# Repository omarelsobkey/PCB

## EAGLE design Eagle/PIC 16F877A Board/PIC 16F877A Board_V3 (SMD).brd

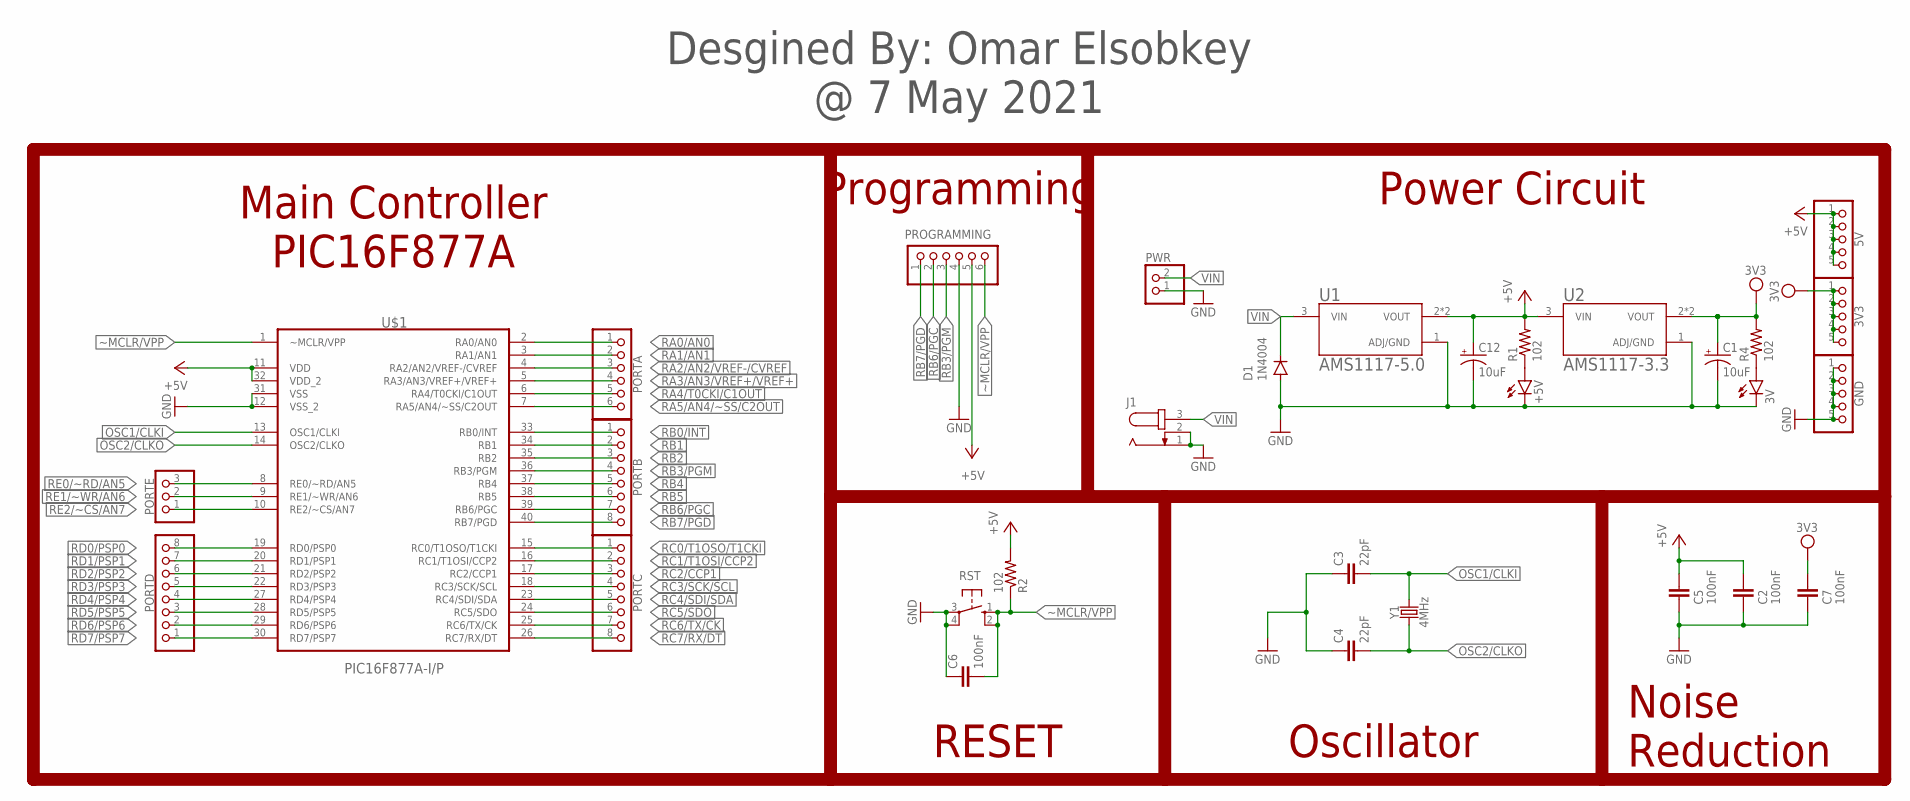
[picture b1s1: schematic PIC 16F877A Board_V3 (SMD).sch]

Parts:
3V: LEDSML0805; SML0805
3V3, 5V: PINHD-1X5; 1X05
+5V: LEDSML0805; SML0805
C1, C12: 10uF; CPOL-RADIAL-2.5MM-5MM-KIT
C2, C5, C6, C7: 100nF; C025-025X050
C3, C4: 22pF; C025-025X050
D1: 1N4004; DO41-10
GND: PINHD-1X5; 1X05
J1: JACK-PLUG0; SPC4077
PORTA: PINHD-1X6; 1X06
PORTB: PINHD-1X8; 1X08
PORTC: PINHD-1X8; 1X08
PORTD: PINHD-1X8; 1X08
PORTE: PINHD-1X3; 1X03
PROGRAMMING: PINHD-1X6; 1X06
PWR: PINHD-1X2; 1X02
R1, R2, R4: 102; 1206
RST: 10-XX; B3F-10XX
U1: AMS1117-5.0
U2: AMS1117-3.3; AMS1117-5.0
U$1: PIC16F877A-I/P; 16F877A
Y1: 4MHz; HC49U

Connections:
3V3: 3V3.1, 3V3.2, 3V3.3, 3V3.4, 3V3.5, C1.1 (+), C7.2, R4.2, U2.2 (VOUT), U2.4 (VOUT)
+5V: 5V.1, 5V.2, 5V.3, 5V.4, 5V.5, C2.2, C5.2, C12.1 (+), PROGRAMMING.5, R1.2, R2.2, U1.2 (VOUT), U1.4 (VOUT), U2.3 (VIN), U$1.11 (VDD), U$1.32 (VDD_2)
GND: 3V.C, +5V.C, C1.2 (-), C2.1, C3.1, C4.1, C5.1, C6.1, C7.1, C12.2 (-), D1.A, GND.1, GND.2, GND.3, GND.4, GND.5, J1.1, J1.2, PROGRAMMING.4, PWR.1, RST.3, RST.4 (P1), U1.1 (ADJ/GND), U2.1 (ADJ/GND), U$1.12 (VSS_2), U$1.31 (VSS)
unnamed: 3V.A, R4.1
unnamed: +5V.A, R1.1
OSC1/CLKI: C3.2, U$1.13 (OSC1/CLKI), Y1.2
OSC2/CLKO: C4.2, U$1.14 (OSC2/CLKO), Y1.1
RA0/AN0: PORTA.1, U$1.2 (RA0/AN0)
RA1/AN1: PORTA.2, U$1.3 (RA1/AN1)
RA2/AN2/VREF-/CVREF: PORTA.3, U$1.4 (RA2/AN2/VREF-/CVREF)
RA3/AN3/VREF+/VREF+: PORTA.4, U$1.5 (RA3/AN3/VREF+/VREF+)
RA4/T0CKI/C1OUT: PORTA.5, U$1.6 (RA4/T0CKI/C1OUT)
RA5/AN4/~SS/C2OUT: PORTA.6, U$1.7 (RA5/AN4/~SS/C2OUT)
RB0/INT: PORTB.1, U$1.33 (RB0/INT)
RB1: PORTB.2, U$1.34 (RB1)
RB2: PORTB.3, U$1.35 (RB2)
RB3/PGM: PORTB.4, PROGRAMMING.3, U$1.36 (RB3/PGM)
RB4: PORTB.5, U$1.37 (RB4)
RB5: PORTB.6, U$1.38 (RB5)
RB6/PGC: PORTB.7, PROGRAMMING.2, U$1.39 (RB6/PGC)
RB7/PGD: PORTB.8, PROGRAMMING.1, U$1.40 (RB7/PGD)
RC0/T1OSO/T1CKI: PORTC.1, U$1.15 (RC0/T1OSO/T1CKI)
RC1/T1OSI/CCP2: PORTC.2, U$1.16 (RC1/T1OSI/CCP2)
RC2/CCP1: PORTC.3, U$1.17 (RC2/CCP1)
RC3/SCK/SCL: PORTC.4, U$1.18 (RC3/SCK/SCL)
RC4/SDI/SDA: PORTC.5, U$1.23 (RC4/SDI/SDA)
RC5/SDO: PORTC.6, U$1.24 (RC5/SDO)
RC6/TX/CK: PORTC.7, U$1.25 (RC6/TX/CK)
RC7/RX/DT: PORTC.8, U$1.26 (RC7/RX/DT)
RD0/PSP0: PORTD.8, U$1.19 (RD0/PSP0)
RD1/PSP1: PORTD.7, U$1.20 (RD1/PSP1)
RD2/PSP2: PORTD.6, U$1.21 (RD2/PSP2)
RD3/PSP3: PORTD.5, U$1.22 (RD3/PSP3)
RD4/PSP4: PORTD.4, U$1.27 (RD4/PSP4)
RD5/PSP5: PORTD.3, U$1.28 (RD5/PSP5)
RD6/PSP6: PORTD.2, U$1.29 (RD6/PSP6)
RD7/PSP7: PORTD.1, U$1.30 (RD7/PSP7)
RE0/~RD/AN5: PORTE.3, U$1.8 (RE0/~RD/AN5)
RE1/~WR/AN6: PORTE.2, U$1.9 (RE1/~WR/AN6)
RE2/~CS/AN7: PORTE.1, U$1.10 (RE2/~CS/AN7)
VIN: D1.C, J1.3, PWR.2, U1.3 (VIN)
~MCLR/VPP: C6.2, PROGRAMMING.6, R2.1, RST.1 (S), RST.2 (S1), U$1.1 (~MCLR/VPP)

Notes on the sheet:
Main Controller PIC16F877A
Power Circuit
RESET
Oscillator
Noise Reduction
Programming
Desgined By: Omar Elsobkey @ 7 May 2021

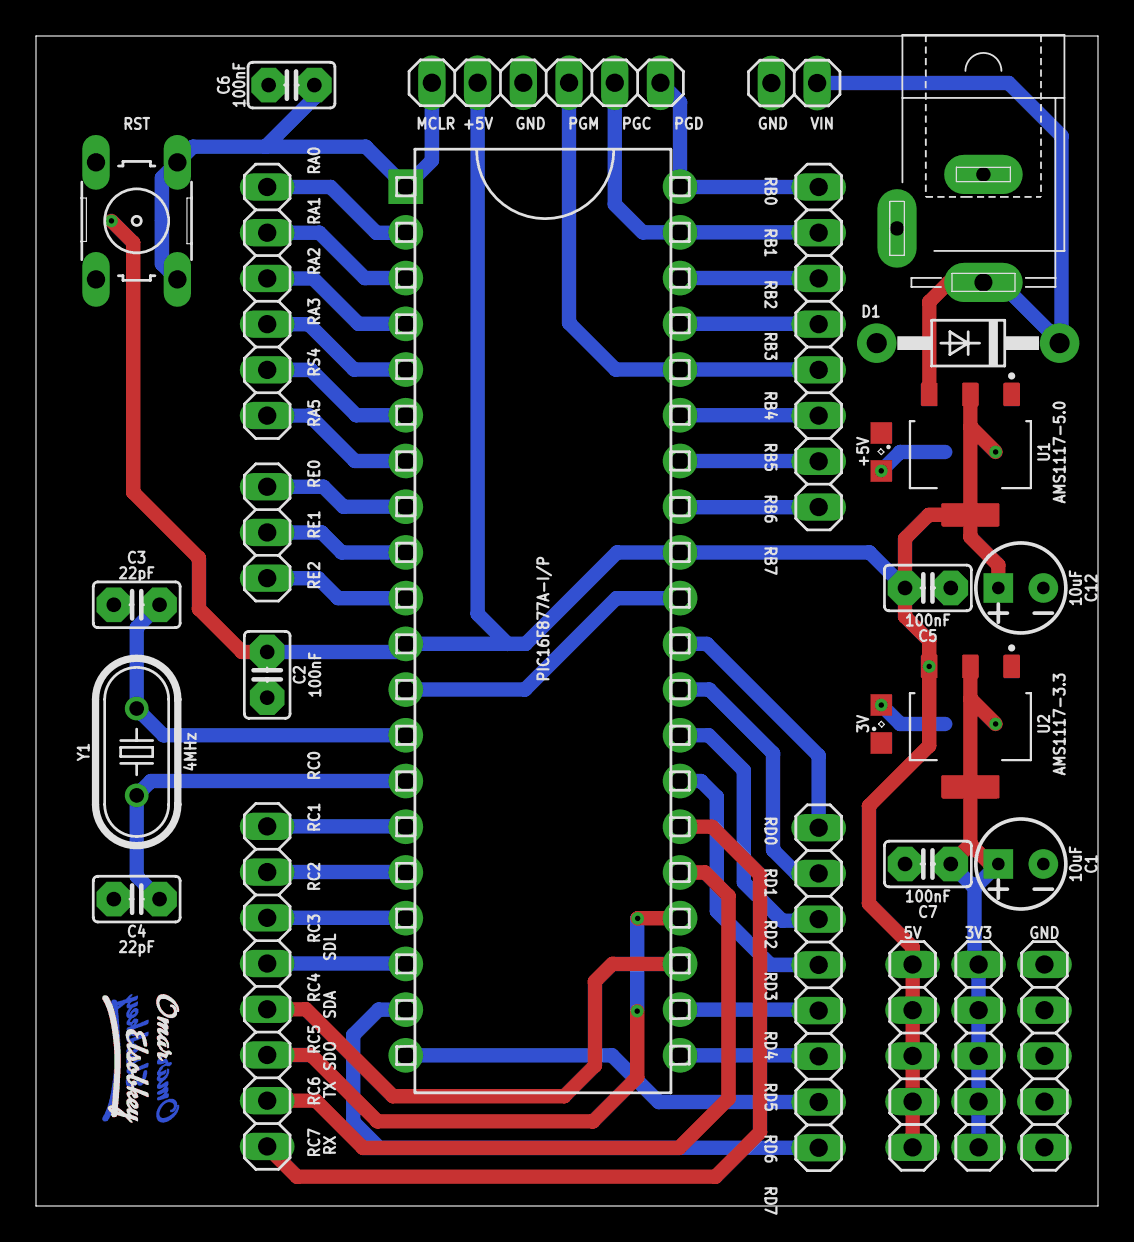
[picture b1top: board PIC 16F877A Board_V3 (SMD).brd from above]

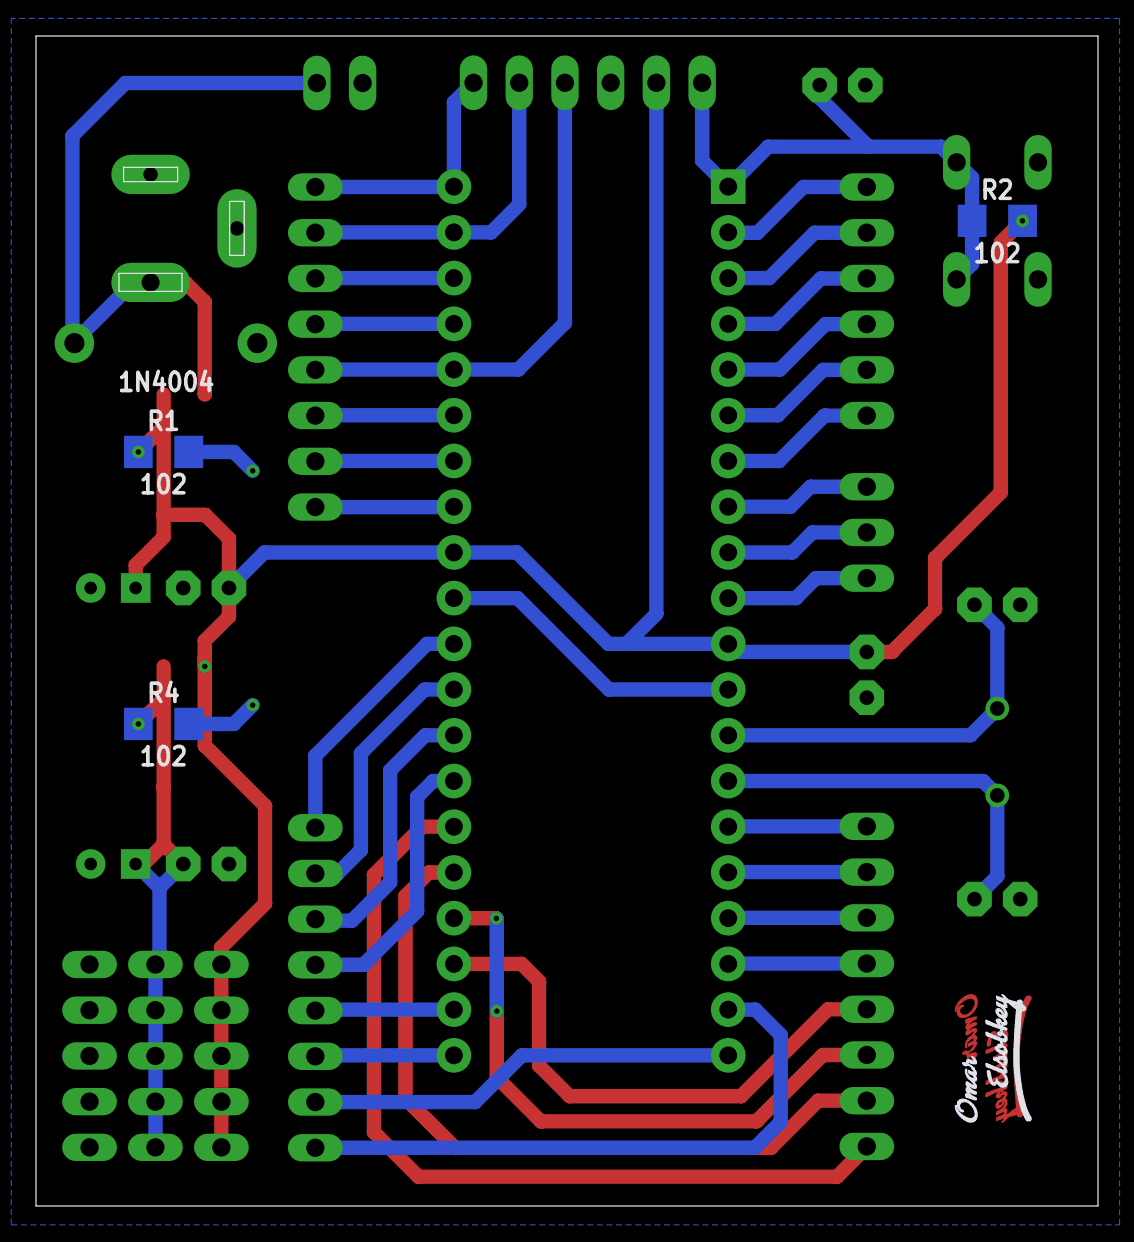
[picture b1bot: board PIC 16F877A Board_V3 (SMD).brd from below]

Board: 2 copper layers, 59.0 x 65.0 mm, 34 parts (5 on the bottom side), 42 nets.

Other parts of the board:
U$2, U$3: OMAR_ELSOBKEY_X0.5_TN
U$4, U$5: OMAR_ELSOBKEY_X0.5_T

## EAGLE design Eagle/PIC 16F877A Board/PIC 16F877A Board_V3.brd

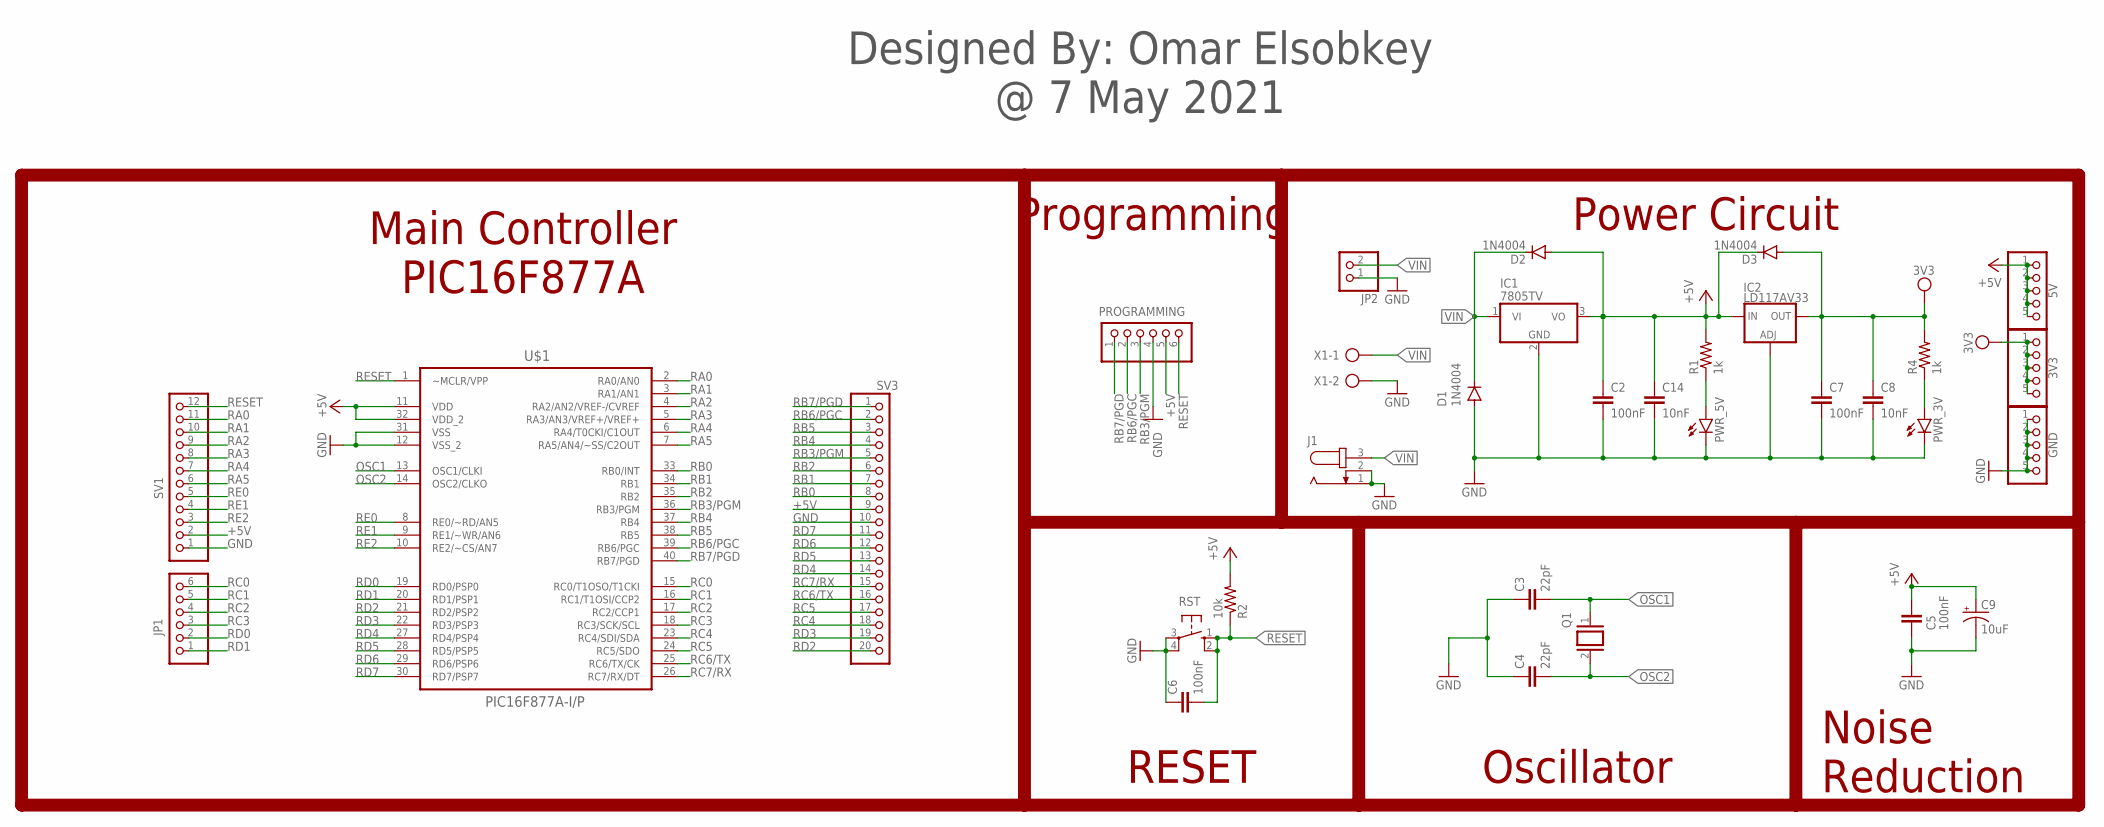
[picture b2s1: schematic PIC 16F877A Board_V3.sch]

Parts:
3V3, 5V: PINHD-1X5; 1X05
C2, C5, C6, C7: 100nF; C025-025X050
C3, C4: 22pF; C025-025X050
C8, C14: 10nF; C025-025X050
C9: 10uF; CPOL-RADIAL-2.5MM-5MM-KIT
D1, D2, D3: 1N4004; DO41-10
GND: PINHD-1X5; 1X05
IC1: 7805TV; TO220V
IC2: LD117AV33; TO220L1
J1: JACK-PLUG0; SPC4077
JP1: PINHD-1X6; 1X06
JP2: PINHD-1X2; 1X02
PROGRAMMING: PINHD-1X6; 1X06
PWR_3V, PWR_5V: LED3MM
Q1: XTAL/S; QS
R1, R4: 1k; AXIAL-0.3
R2: 10k; AXIAL-0.3
RST: 10-XX; B3F-10XX
SV1: PINHD-1X12; 1X12
SV3: PINHD-1X20; 1X20
U$1: PIC16F877A-I/P; 16F877A
X1: AK500/2-H

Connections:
3V3: 3V3.1, 3V3.2, 3V3.3, 3V3.4, 3V3.5, C7.1, C8.1, D3.A, IC2.2 (OUT), R4.P$2 (2)
+5V: 5V.1, 5V.2, 5V.3, 5V.4, 5V.5, C2.1, C5.2, C9.1 (+), C14.1, D2.A, D3.C, IC1.3 (VO), IC2.3 (IN), PROGRAMMING.5, R1.P$2 (2), R2.P$2 (2), SV1.2, SV3.9, U$1.11 (VDD), U$1.32 (VDD_2)
GND: C2.2, C3.1, C4.1, C5.1, C6.1, C7.2, C8.2, C9.2 (-), C14.2, D1.A, GND.1, GND.2, GND.3, GND.4, GND.5, IC1.2 (GND), IC2.1 (ADJ), J1.1, J1.2, JP2.1, PROGRAMMING.4, PWR_3V.K (C), PWR_5V.K (C), RST.3, RST.4 (P1), SV1.1, SV3.10, U$1.12 (VSS_2), U$1.31 (VSS), X1.2
unnamed: PWR_3V.A, R4.P$1 (1)
unnamed: PWR_5V.A, R1.P$1 (1)
OSC1: C3.2, Q1.1, U$1.13 (OSC1/CLKI)
OSC2: C4.2, Q1.2, U$1.14 (OSC2/CLKO)
RA0: SV1.11, U$1.2 (RA0/AN0)
RA1: SV1.10, U$1.3 (RA1/AN1)
RA2: SV1.9, U$1.4 (RA2/AN2/VREF-/CVREF)
RA3: SV1.8, U$1.5 (RA3/AN3/VREF+/VREF+)
RA4: SV1.7, U$1.6 (RA4/T0CKI/C1OUT)
RA5: SV1.6, U$1.7 (RA5/AN4/~SS/C2OUT)
RB0: SV3.8, U$1.33 (RB0/INT)
RB1: SV3.7, U$1.34 (RB1)
RB2: SV3.6, U$1.35 (RB2)
RB3/PGM: PROGRAMMING.3, SV3.5, U$1.36 (RB3/PGM)
RB4: SV3.4, U$1.37 (RB4)
RB5: SV3.3, U$1.38 (RB5)
RB6/PGC: PROGRAMMING.2, SV3.2, U$1.39 (RB6/PGC)
RB7/PGD: PROGRAMMING.1, SV3.1, U$1.40 (RB7/PGD)
RC0: JP1.6, U$1.15 (RC0/T1OSO/T1CKI)
RC1: JP1.5, U$1.16 (RC1/T1OSI/CCP2)
RC2: JP1.4, U$1.17 (RC2/CCP1)
RC3: JP1.3, U$1.18 (RC3/SCK/SCL)
RC4: SV3.18, U$1.23 (RC4/SDI/SDA)
RC5: SV3.17, U$1.24 (RC5/SDO)
RC6/TX: SV3.16, U$1.25 (RC6/TX/CK)
RC7/RX: SV3.15, U$1.26 (RC7/RX/DT)
RD0: JP1.2, U$1.19 (RD0/PSP0)
RD1: JP1.1, U$1.20 (RD1/PSP1)
RD2: SV3.20, U$1.21 (RD2/PSP2)
RD3: SV3.19, U$1.22 (RD3/PSP3)
RD4: SV3.14, U$1.27 (RD4/PSP4)
RD5: SV3.13, U$1.28 (RD5/PSP5)
RD6: SV3.12, U$1.29 (RD6/PSP6)
RD7: SV3.11, U$1.30 (RD7/PSP7)
RE0: SV1.5, U$1.8 (RE0/~RD/AN5)
RE1: SV1.4, U$1.9 (RE1/~WR/AN6)
RE2: SV1.3, U$1.10 (RE2/~CS/AN7)
RESET: C6.2, PROGRAMMING.6, R2.P$1 (1), RST.1 (S), RST.2 (S1), SV1.12, U$1.1 (~MCLR/VPP)
VIN: D1.C, D2.C, IC1.1 (VI), J1.3, JP2.2, X1.1

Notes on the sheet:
Main Controller PIC16F877A
Power Circuit
RESET
Oscillator
Noise Reduction
Programming
Designed By: Omar Elsobkey @ 7 May 2021

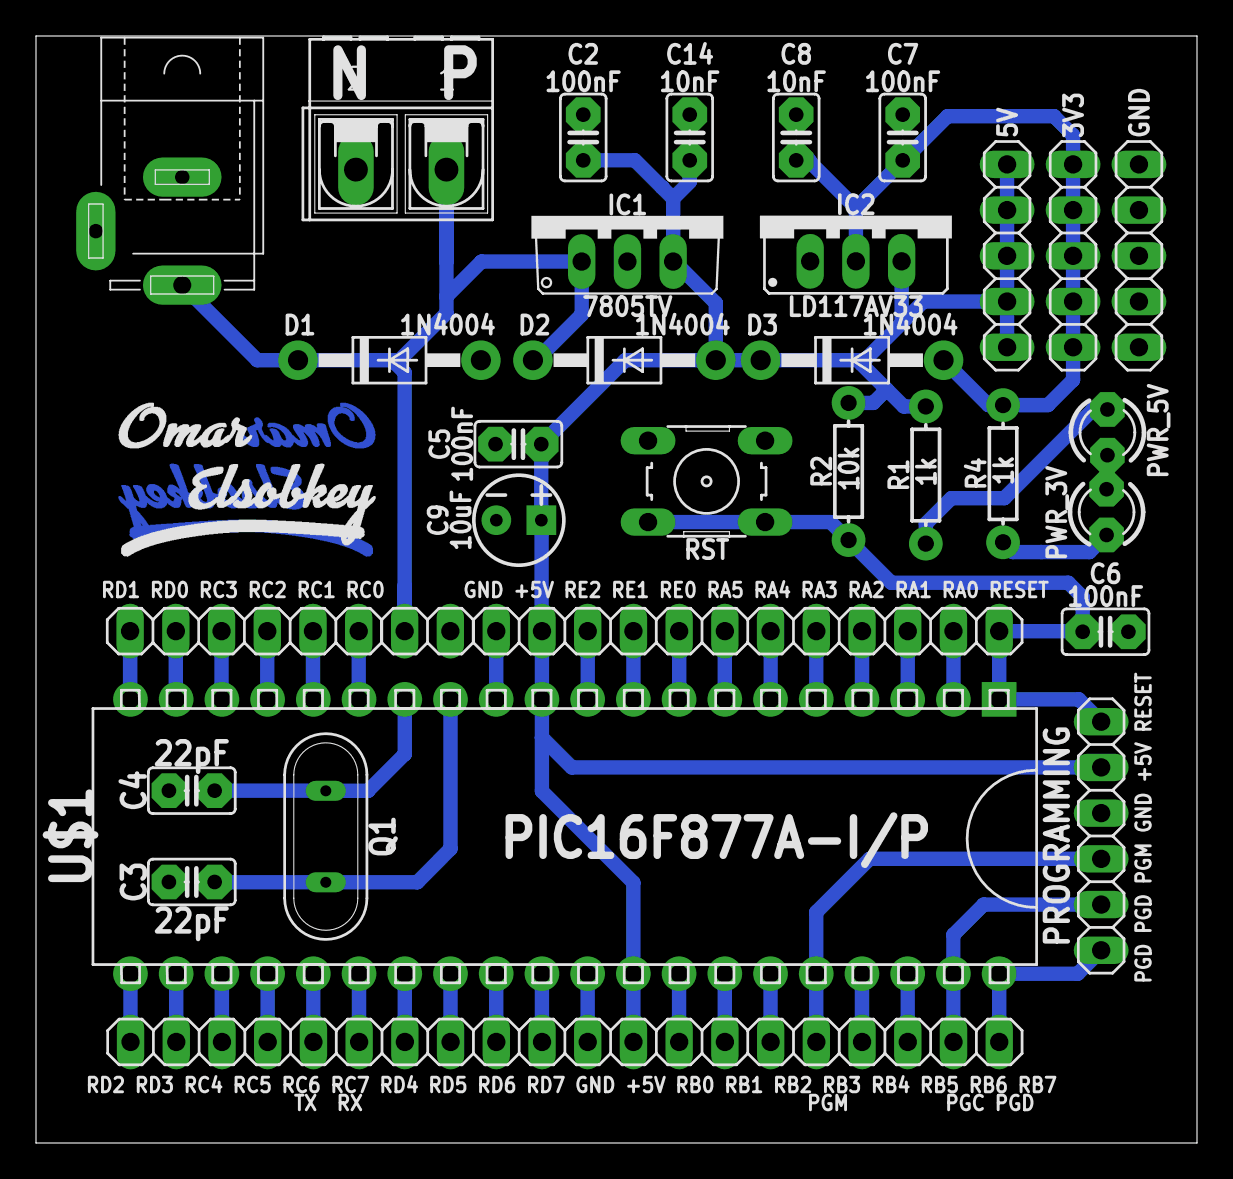
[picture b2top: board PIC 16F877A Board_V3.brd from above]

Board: 2 copper layers, 64.5 x 61.5 mm, 34 parts (1 on the bottom side), 42 nets.

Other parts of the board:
U$2: OMAR_ELSOBKEY_X1_T
U$3: OMAR_ELSOBKEY_X1_TN

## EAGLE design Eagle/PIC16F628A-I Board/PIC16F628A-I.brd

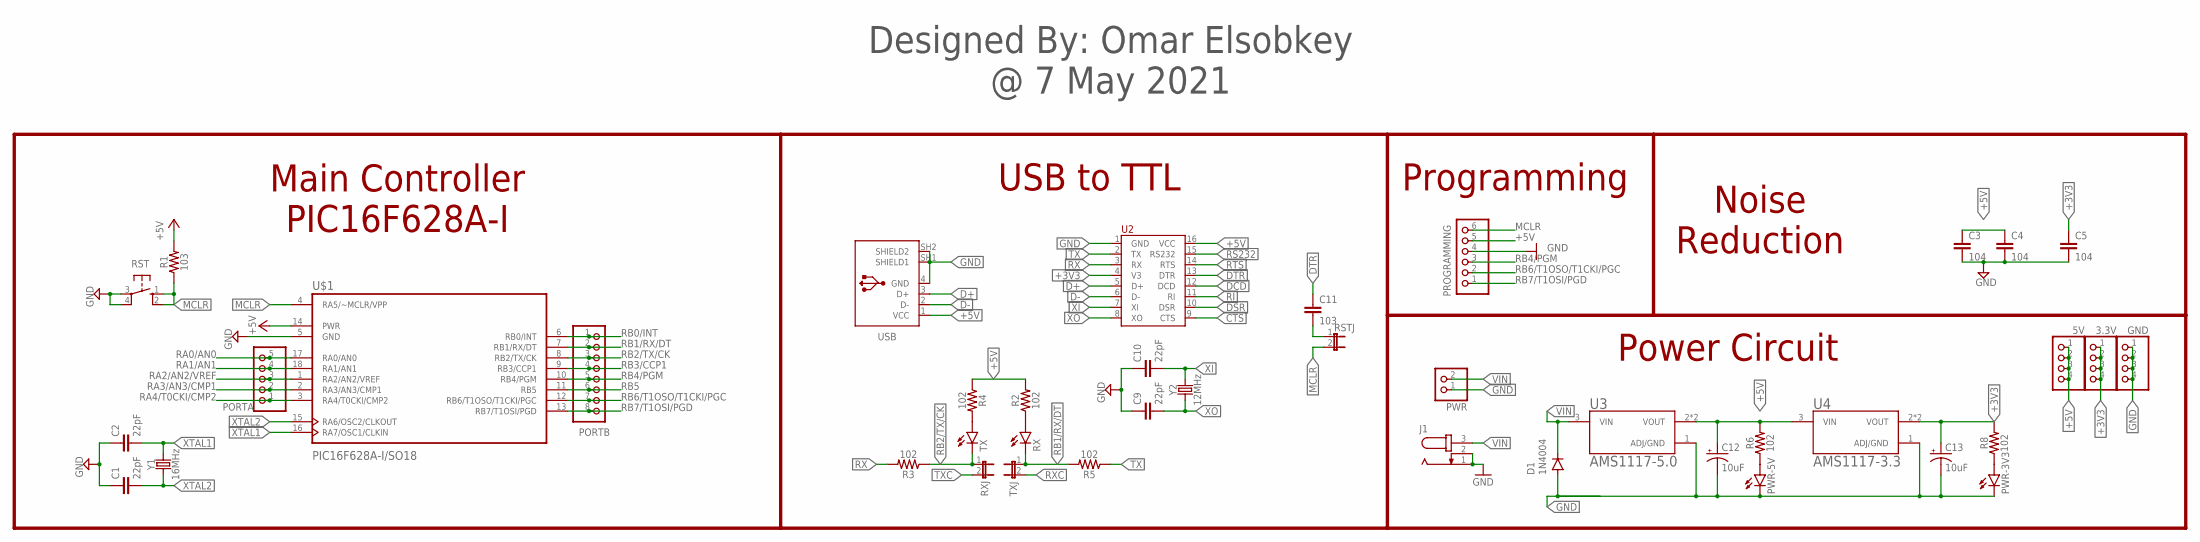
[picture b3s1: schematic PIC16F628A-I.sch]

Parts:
3.3V, 5V: PINHD-1X4; 1X04
C1, C2, C9, C10: 22pF; CAP-PTH-2.54
C3, C4, C5: 104; CAP-PTH-2.54
C11: 103; CAP-PTH-2.54
C12, C13: 10uF; CPOL-RADIAL-2.5MM-5MM-KIT
D1: 1N4004; DO41-10
GND: PINHD-1X4; 1X04
J1: JACK-PLUG0; SPC4077
PORTA: PINHD-1X5; 1X05
PORTB: PINHD-1X8; 1X08
PROGRAMMING: PINHD-1X6; 1X06
PWR: PINHD-1X2; 1X02
PWR-3V3, PWR-5V: LEDCHIP-LED0805; CHIP-LED0805
R1: 103; 1206
R2, R3, R4, R5, R6, R8: 102; 1206
RST: 10-XX; B3F-10XX
RSTJ: JP1E; JP1
RX: LEDCHIP-LED0805; CHIP-LED0805
RXJ: JP1E; JP1
TX: LEDCHIP-LED0805; CHIP-LED0805
TXJ: JP1E; JP1
U2: CH340G; SOP-16
U3: AMS1117-5.0
U4: AMS1117-3.3; AMS1117-5.0
U$1: PIC16F628A-I/SO18; SOIC127P1030X265-18N
USB: 61729-1011; 61729-1011BLF
Y1: 16MHz; HC49U
Y2: 12MHz; HC49U

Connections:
+3V3: 3.3V.1, 3.3V.2, 3.3V.3, 3.3V.4, C5.1, C13.1 (+), R8.2, U2.4 (V3), U4.2 (VOUT), U4.4 (VOUT)
+5V: 5V.1, 5V.2, 5V.3, 5V.4, C3.1, C4.1, C12.1 (+), PROGRAMMING.5, R1.2, R2.2, R4.1, R6.2, U2.16 (VCC), U3.2 (VOUT), U3.4 (VOUT), U4.3 (VIN), U$1.14 (PWR), USB.1 (VCC)
CTS: U2.9 (CTS)
D+: U2.5 (D+), USB.3 (D+)
D-: U2.6 (D-), USB.2 (D-)
DCD: U2.12 (DCD)
DSR: U2.10 (DSR)
DTR: C11.1, U2.13 (DTR)
GND: C1.1, C2.1, C3.2, C4.2, C5.2, C9.1, C10.1, C12.2 (-), C13.2 (-), D1.A, GND.1, GND.2, GND.3, GND.4, J1.1, J1.2, PROGRAMMING.4, PWR.1, PWR-3V3.C, PWR-5V.C, RST.3, RST.4 (P1), U2.1 (GND), U3.1 (ADJ/GND), U4.1 (ADJ/GND), U$1.5 (GND), USB.4 (GND), USB.SH1 (SHIELD1), USB.SH2 (SHIELD2)
MCLR: PROGRAMMING.6, R1.1, RST.1 (S), RST.2 (S1), RSTJ.2, U$1.4 (RA5/~MCLR/VPP)
unnamed: R2.1, RX.A
unnamed: R4.2, TX.A
unnamed: PWR-5V.A, R6.1
unnamed: PWR-3V3.A, R8.1
unnamed: C11.2, RSTJ.1
RA0/AN0: PORTA.5, U$1.17 (RA0/AN0)
RA1/AN1: PORTA.4, U$1.18 (RA1/AN1)
RA2/AN2/VREF: PORTA.3, U$1.1 (RA2/AN2/VREF)
RA3/AN3/CMP1: PORTA.2, U$1.2 (RA3/AN3/CMP1)
RA4/T0CKI/CMP2: PORTA.1, U$1.3 (RA4/T0CKI/CMP2)
RB0/INT: PORTB.1, U$1.6 (RB0/INT)
RB1/RX/DT: PORTB.2, R5.2, RX.C, TXJ.1, U$1.7 (RB1/RX/DT)
RB2/TX/CK: PORTB.3, R3.1, RXJ.1, TX.C, U$1.8 (RB2/TX/CK)
RB3/CCP1: PORTB.4, U$1.9 (RB3/CCP1)
RB4/PGM: PORTB.5, PROGRAMMING.3, U$1.10 (RB4/PGM)
RB5: PORTB.6, U$1.11 (RB5)
RB6/T1OSO/T1CKI/PGC: PORTB.7, PROGRAMMING.2, U$1.12 (RB6/T1OSO/T1CKI/PGC)
RB7/T1OSI/PGD: PORTB.8, PROGRAMMING.1, U$1.13 (RB7/T1OSI/PGD)
RI: U2.11 (RI)
RS232: U2.15 (RS232)
RTS: U2.14 (RTS)
RX: R3.2, U2.3 (RX)
RXC: TXJ.2
TX: R5.1, U2.2 (TX)
TXC: RXJ.2
VIN: D1.C, J1.3, PWR.2, U3.3 (VIN)
XI: C10.2, U2.7 (XI), Y2.2
XO: C9.2, U2.8 (XO), Y2.1
XTAL1: C2.2, U$1.16 (RA7/OSC1/CLKIN), Y1.2
XTAL2: C1.2, U$1.15 (RA6/OSC2/CLKOUT), Y1.1

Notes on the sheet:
Main Controller PIC16F628A-I
USB to TTL
Programming
Noise Reduction
Power Circuit
Designed By: Omar Elsobkey @ 7 May 2021

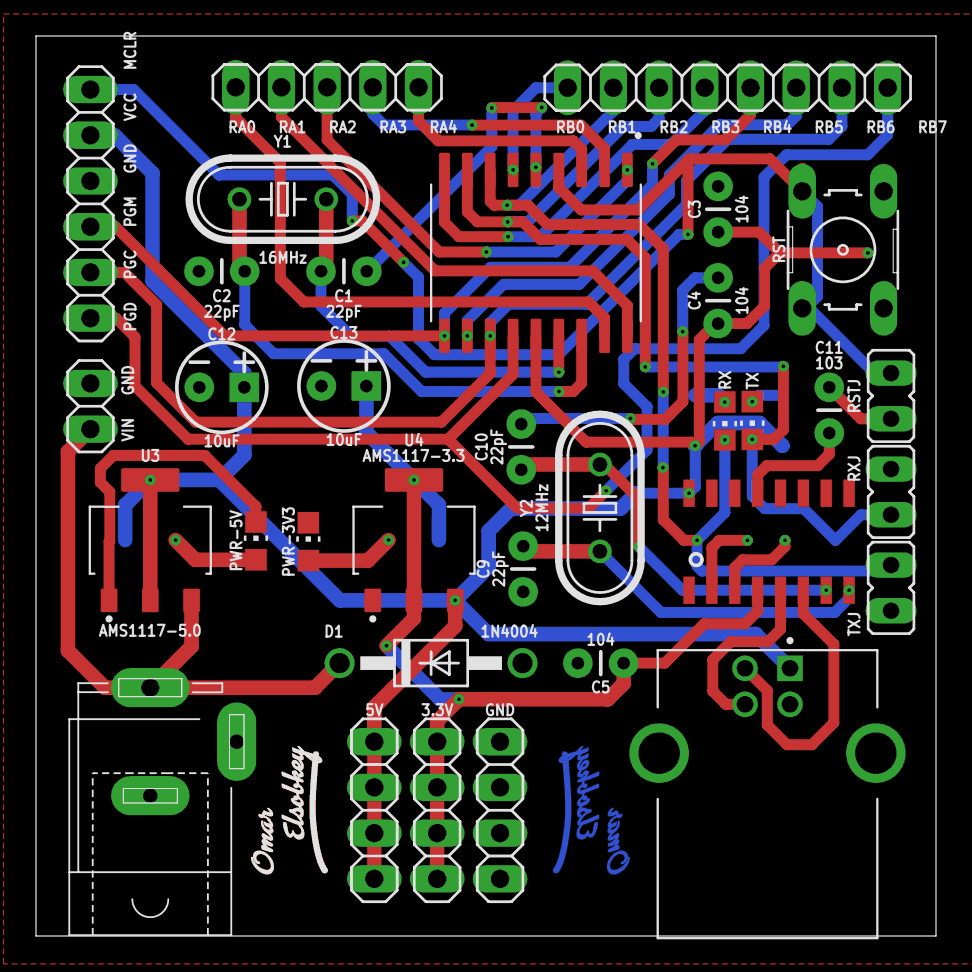
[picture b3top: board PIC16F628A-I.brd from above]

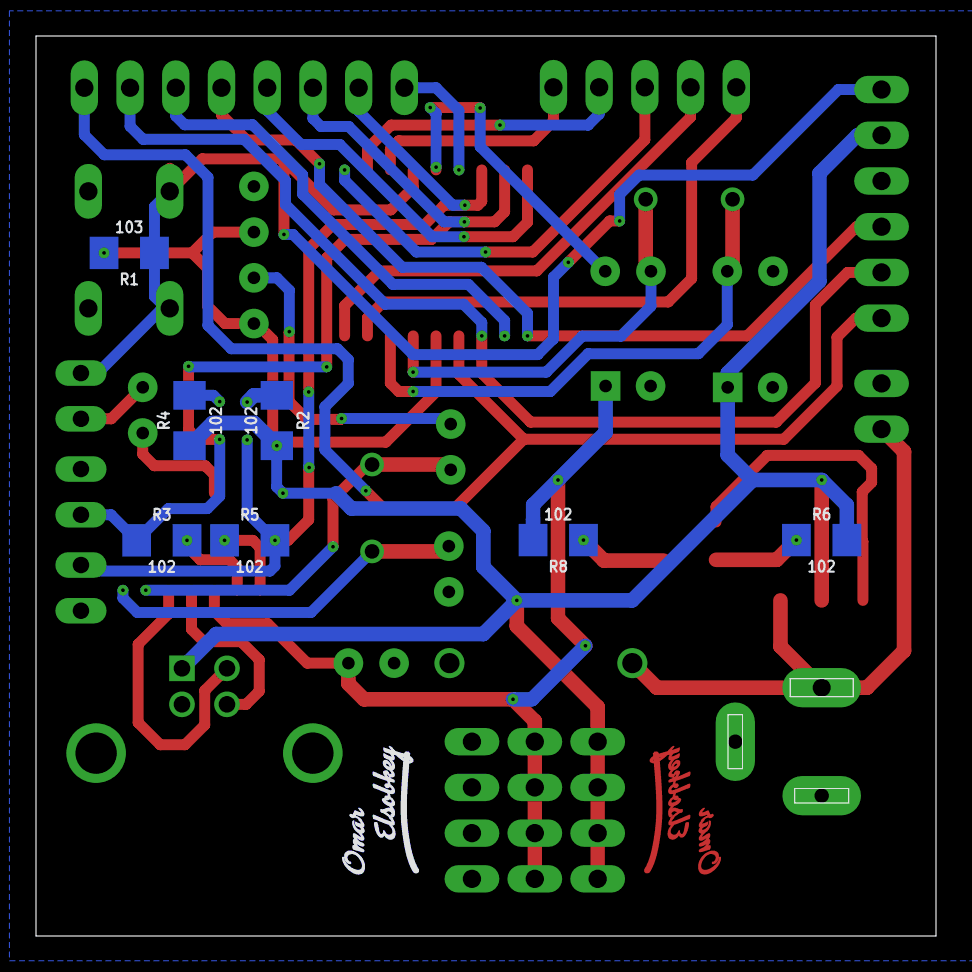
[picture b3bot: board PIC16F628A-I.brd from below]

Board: 2 copper layers, 50.0 x 50.0 mm, 45 parts (9 on the bottom side), 32 nets.

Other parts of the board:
U$2, U$3: OMAR_ELSOBKEY_X0.5_TN
U$4, U$5: OMAR_ELSOBKEY_X0.5_T

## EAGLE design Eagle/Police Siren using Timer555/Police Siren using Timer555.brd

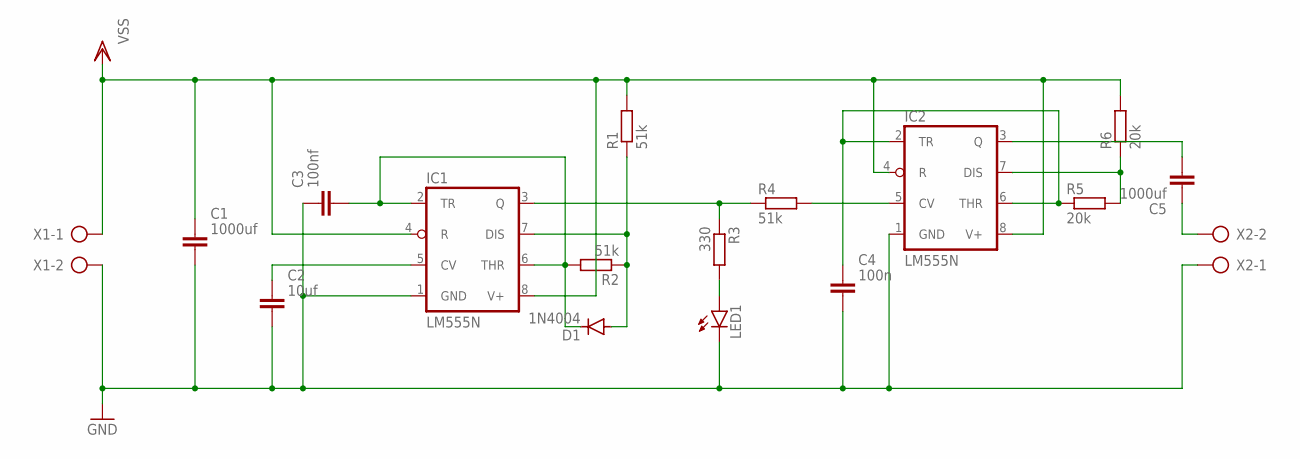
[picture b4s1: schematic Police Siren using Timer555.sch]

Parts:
C1, C5: 1000uf; CAPRD550W60D1025H1250B
C2: 10uf; CAPRD550W60D1025H1250B
C3: 100nf; CAPRD550W60D1025H1250B
C4: 100n; CAPRD550W60D1025H1250B
D1: 1N4004; DO41-10
IC1, IC2: LM555N; DIL08
LED1: LED3MM
R1, R2, R4: 51k; 0204/7
R3: 330; 0204/7
R5, R6: 20k; 0204/7
X1, X2: AK300/2

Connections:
GND: C1.2, C2.2, C3.1, C4.2, IC1.1 (GND), IC2.1 (GND), LED1.K (C), X1.2, X2.1
unnamed: IC1.3 (Q), R3.1, R4.1
unnamed: LED1.A, R3.2
unnamed: C2.1, IC1.5 (CV)
unnamed: C3.2, D1.C, IC1.2 (TR), IC1.6 (THR), R2.2
unnamed: IC2.5 (CV), R4.2
unnamed: D1.A, IC1.7 (DIS), R1.1, R2.1
unnamed: C5.2, IC2.3 (Q)
unnamed: C5.1, X2.2
unnamed: C4.1, IC2.2 (TR), IC2.6 (THR), R5.1
unnamed: IC2.7 (DIS), R5.2, R6.1
VSS: C1.1, IC1.4 (R), IC1.8 (V+), IC2.4 (R), IC2.8 (V+), R1.2, R6.2, X1.1

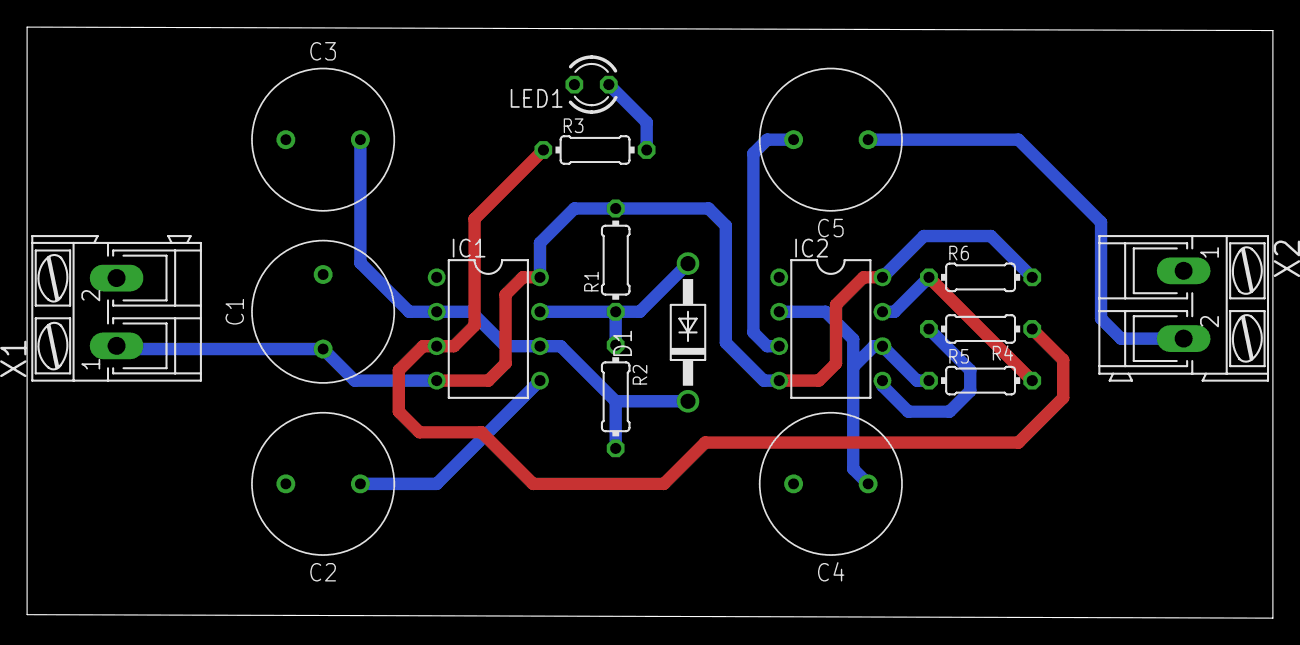
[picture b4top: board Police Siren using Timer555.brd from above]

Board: 2 copper layers, 91.9 x 43.6 mm, 17 parts (0 on the bottom side), 12 nets.

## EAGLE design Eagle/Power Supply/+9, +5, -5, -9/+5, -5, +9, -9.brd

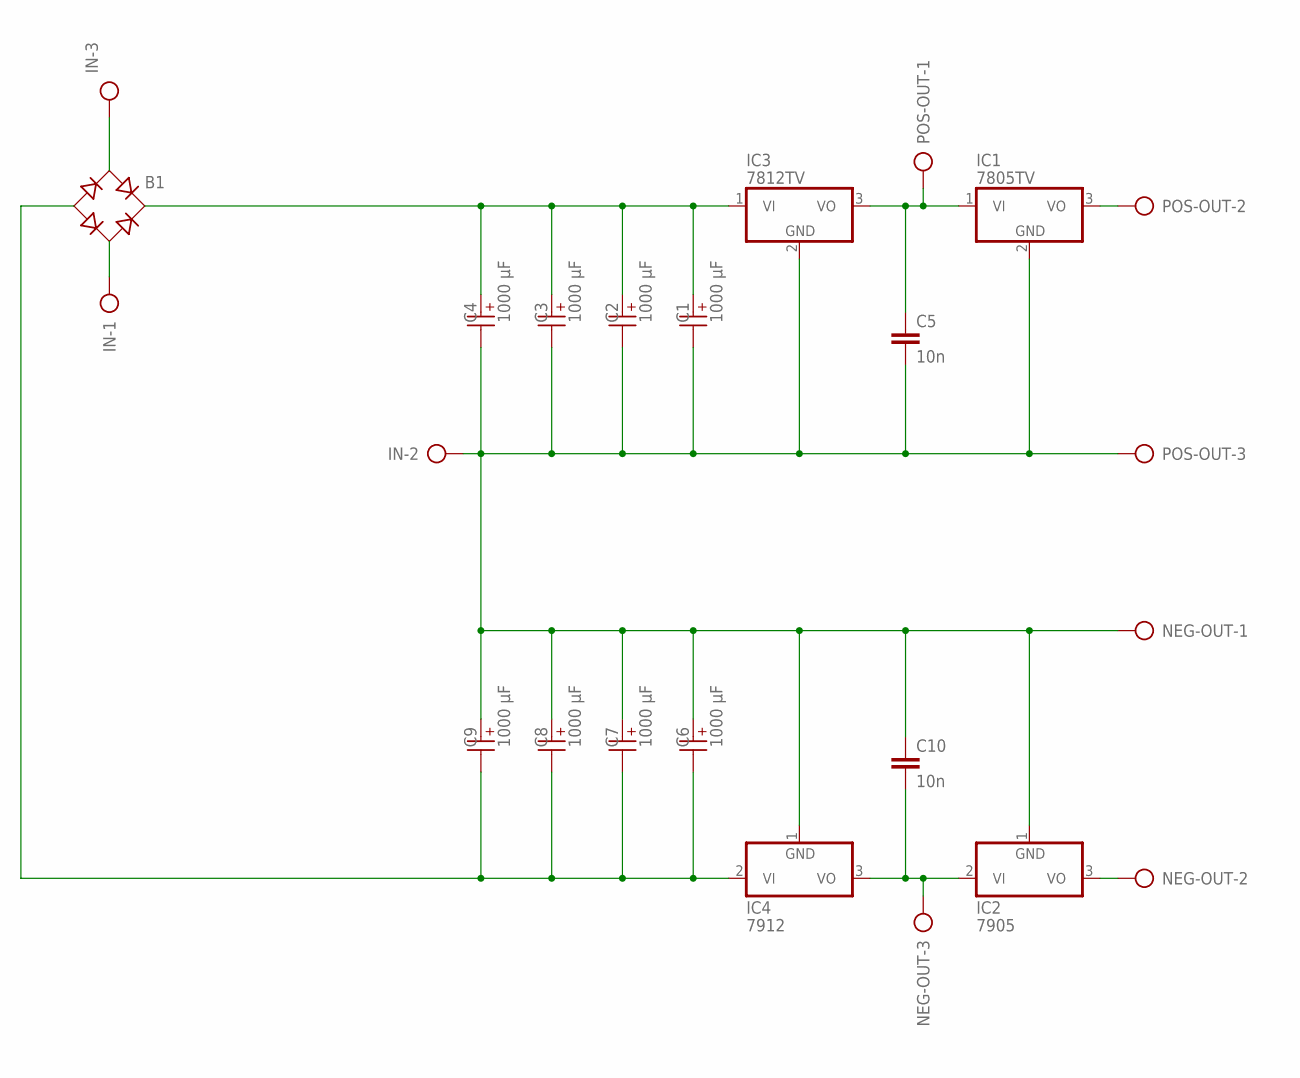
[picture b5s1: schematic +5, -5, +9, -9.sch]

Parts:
B1: RB1A
C1, C2, C3, C4, C6, C7, C8, C9: 1000 µF; WCAP-ATG8_10X12.5(DXL)
C5, C10: 10n; C025-025X050
IC1: 7805TV; TO220V
IC2: 7905; TO220H
IC3: 7812TV; TO220V
IC4: 7912; TO220H
IN: AK300/3
NEG-OUT: AK300/3
POS-OUT: AK300/3

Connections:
GND: C1.2 (-), C2.2 (-), C3.2 (-), C4.2 (-), C5.2, C6.1 (+), C7.1 (+), C8.1 (+), C9.1 (+), C10.1, IC1.2 (GND), IC2.1 (GND), IC3.2 (GND), IC4.1 (GND), IN.2, NEG-OUT.1, POS-OUT.3
unnamed: B1.AC1, IN.3
unnamed: B1.AC2, IN.1
unnamed: B1.+, C1.1 (+), C2.1 (+), C3.1 (+), C4.1 (+), IC3.1 (VI)
unnamed: IC2.3 (VO), NEG-OUT.2
unnamed: IC1.3 (VO), POS-OUT.2
unnamed: B1.-, C6.2 (-), C7.2 (-), C8.2 (-), C9.2 (-), IC4.2 (VI)
unnamed: C5.1, IC1.1 (VI), IC3.3 (VO), POS-OUT.1
unnamed: C10.2, IC2.2 (VI), IC4.3 (VO), NEG-OUT.3

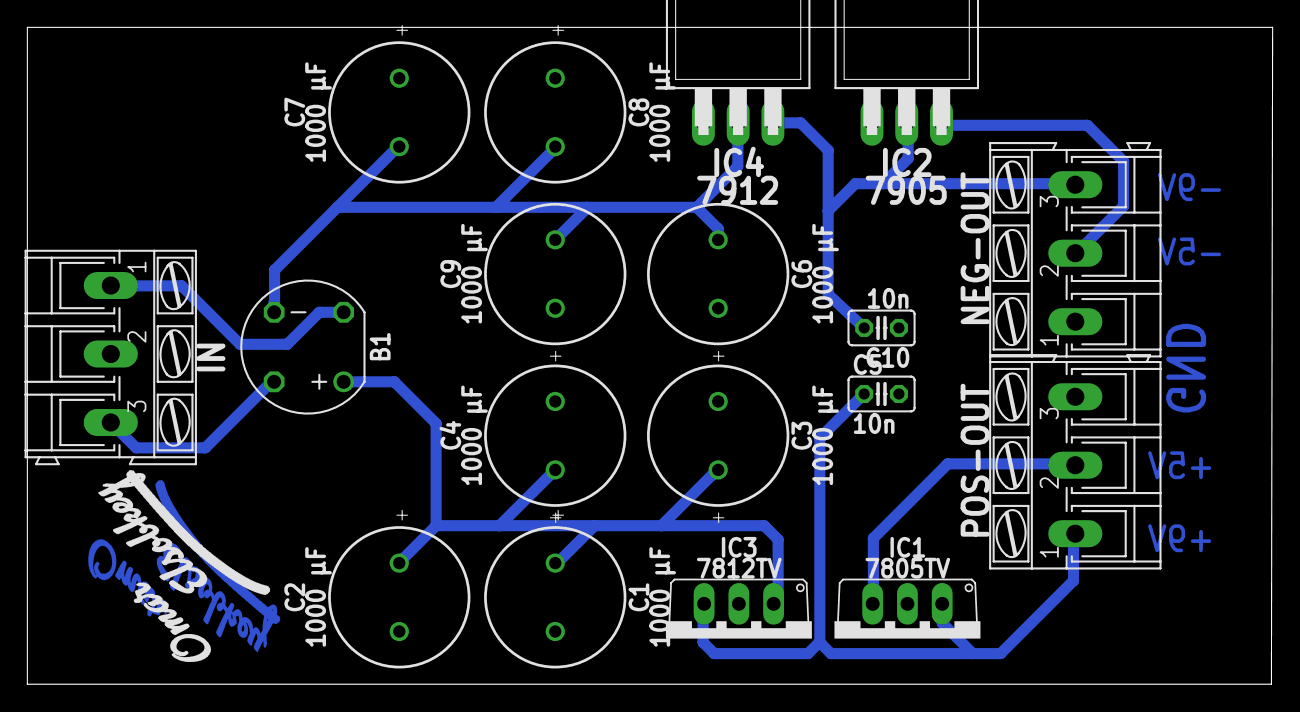
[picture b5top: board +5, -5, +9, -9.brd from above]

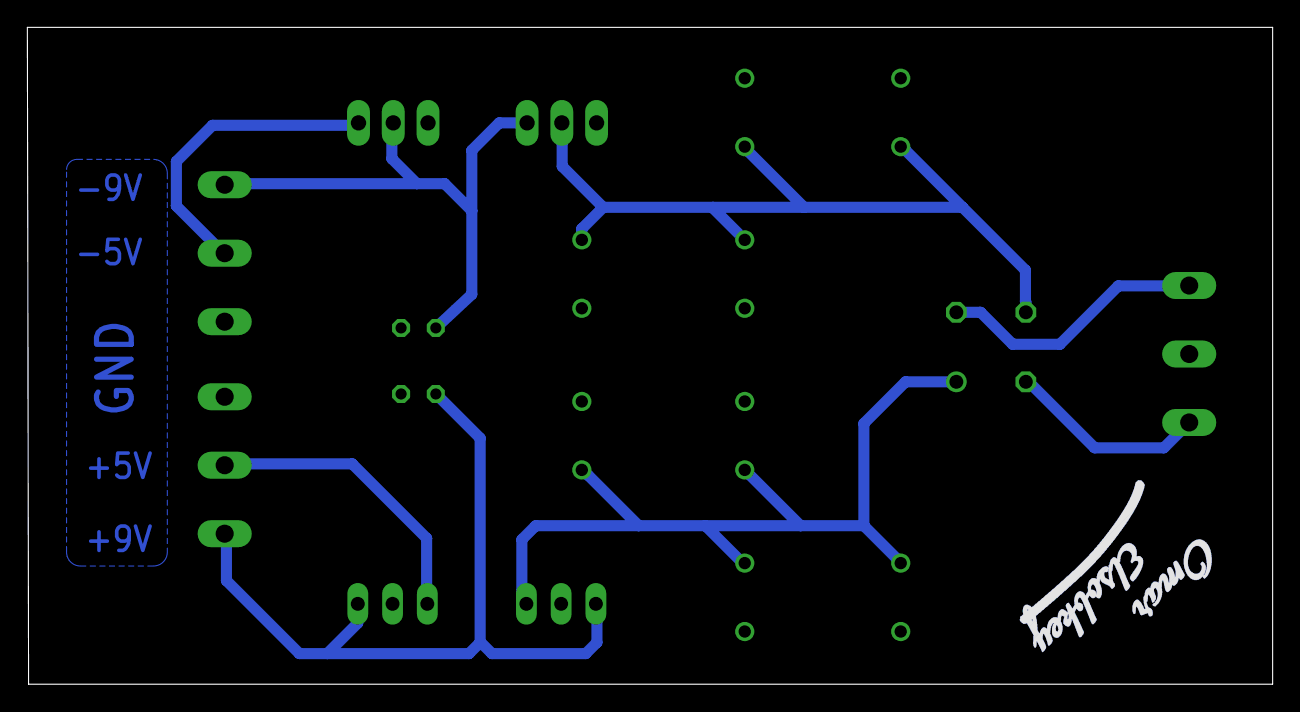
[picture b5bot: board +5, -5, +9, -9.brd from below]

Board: 2 copper layers, 91.0 x 48.0 mm, 21 parts (2 on the bottom side), 9 nets.

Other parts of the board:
U$1: OMAR_ELSOBKEY_X1_T
U$2, U$4: OMAR_ELSOBKEY_X1_TN

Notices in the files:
parts and their libraries:
SparkFun-Capacitors: Licensing: Creative Commons ShareAlike 4.0 International - https://creativecommons.org/licenses/by-sa/4.0
Aluminium Electrolyt Capacitors: Copyright: Würth Elektronik
